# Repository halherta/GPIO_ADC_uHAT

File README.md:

# IO uHat for Raspberry Pi Zero 2W

An expansion board (uHat) for the Raspberry Pi Zero 2W that provides additional GPIO and analog input capabilities through I2C and SPI interfaces.

## Features

- **16 Additional GPIO Pins**: MCP23017 I2C GPIO expander
- **8-Channel 12-bit ADC**: MCP3208 SPI analog-to-digital converter
- **I2C EEPROM**: Compliant with Raspberry Pi uHat specification
- **Hand-Solder Friendly**: SOIC packages for ICs, 1206 packages for passives
- **3.3V Operation**: Compatible with Raspberry Pi GPIO voltage levels

## Hardware Specifications

### GPIO Expander (MCP23017)
- **Interface**: I2C
- **I2C Address**: 0x20
- **GPIO Pins**: 16 general-purpose input/output pins
- **Logic Level**: 3.3V only

### ADC (MCP3208)
- **Interface**: SPI
- **Channels**: 8 single-ended or 4 differential
- **Resolution**: 12-bit
- **Reference Voltage**: 3.3V
- **Input Range**: 0V to 3.3V

### Power Requirements
- **Supply Voltage**: 3.3V from Raspberry Pi
- **Power Source**: Raspberry Pi GPIO header

## Hardware Design

The board features a compact uHat form factor designed for the Raspberry Pi Zero 2W. All components use hand-solder-friendly packages:
- SOIC packages for integrated circuits
- 1206 packages for resistors and capacitors

### Documentation
- [Schematic (PDF)](https://hussamtalkstech.com/wp-content/uploads/GPIO_ADC_uHAT_schematic.pdf)
- KiCad design files available in this repository

## Software

### Python Classes

Two Python classes are provided for easy interfacing:

1. **MCP23017 GPIO Control**: Configure and control the 16 GPIO pins
2. **MCP3208 ADC Interface**: Perform analog-to-digital conversions

### Demo Application

A demonstration program is included that showcases the board's capabilities:
- Reads analog voltage from a potentiometer (connected to ADC)
- Controls a 10-LED bargraph display (connected to GPIO expander)
- LEDs illuminate proportionally to the input voltage (0V = all off, 3.3V = all on)

### Setup

```bash
# Enable I2C and SPI interfaces
sudo raspi-config
# Navigate to Interface Options and enable I2C and SPI

# Verify I2C device detection
i2cdetect -y 1
# Should show device at address 0x20

# Clone repository and run demo
git clone https://github.com/halherta/GPIO_ADC_uHAT
cd GPIO_ADC_uHAT/test_code
python3 demo.py
```

## Getting Started

### Prerequisites
- Raspberry Pi Zero 2W
- Python 3
- I2C and SPI interfaces enabled
- Required Python libraries:
  - `smbus2` (for I2C communication)
  - `spidev` (for SPI communication)

### Installation

1. Clone this repository:
```bash
git clone https://github.com/halherta/GPIO_ADC_uHAT
```

2. Install required Python packages:
```bash
pip3 install smbus2 spidev
```

3. Run the demo program:
```bash
cd test_code
python3 demo.py
```

## License

This project is open source and available for use under the terms specified in the repository.

## Related Posts

For more detailed information about this project, visit:
- [IO uHat Blog Post](https://hussamtalkstech.com/rpi-io-uhat/)
- Future posts will cover EEPROM configuration and additional applications

## Contributing

Contributions, issues, and feature requests are welcome!

- Designed with KiCad
- Compatible with Raspberry Pi uHat specification

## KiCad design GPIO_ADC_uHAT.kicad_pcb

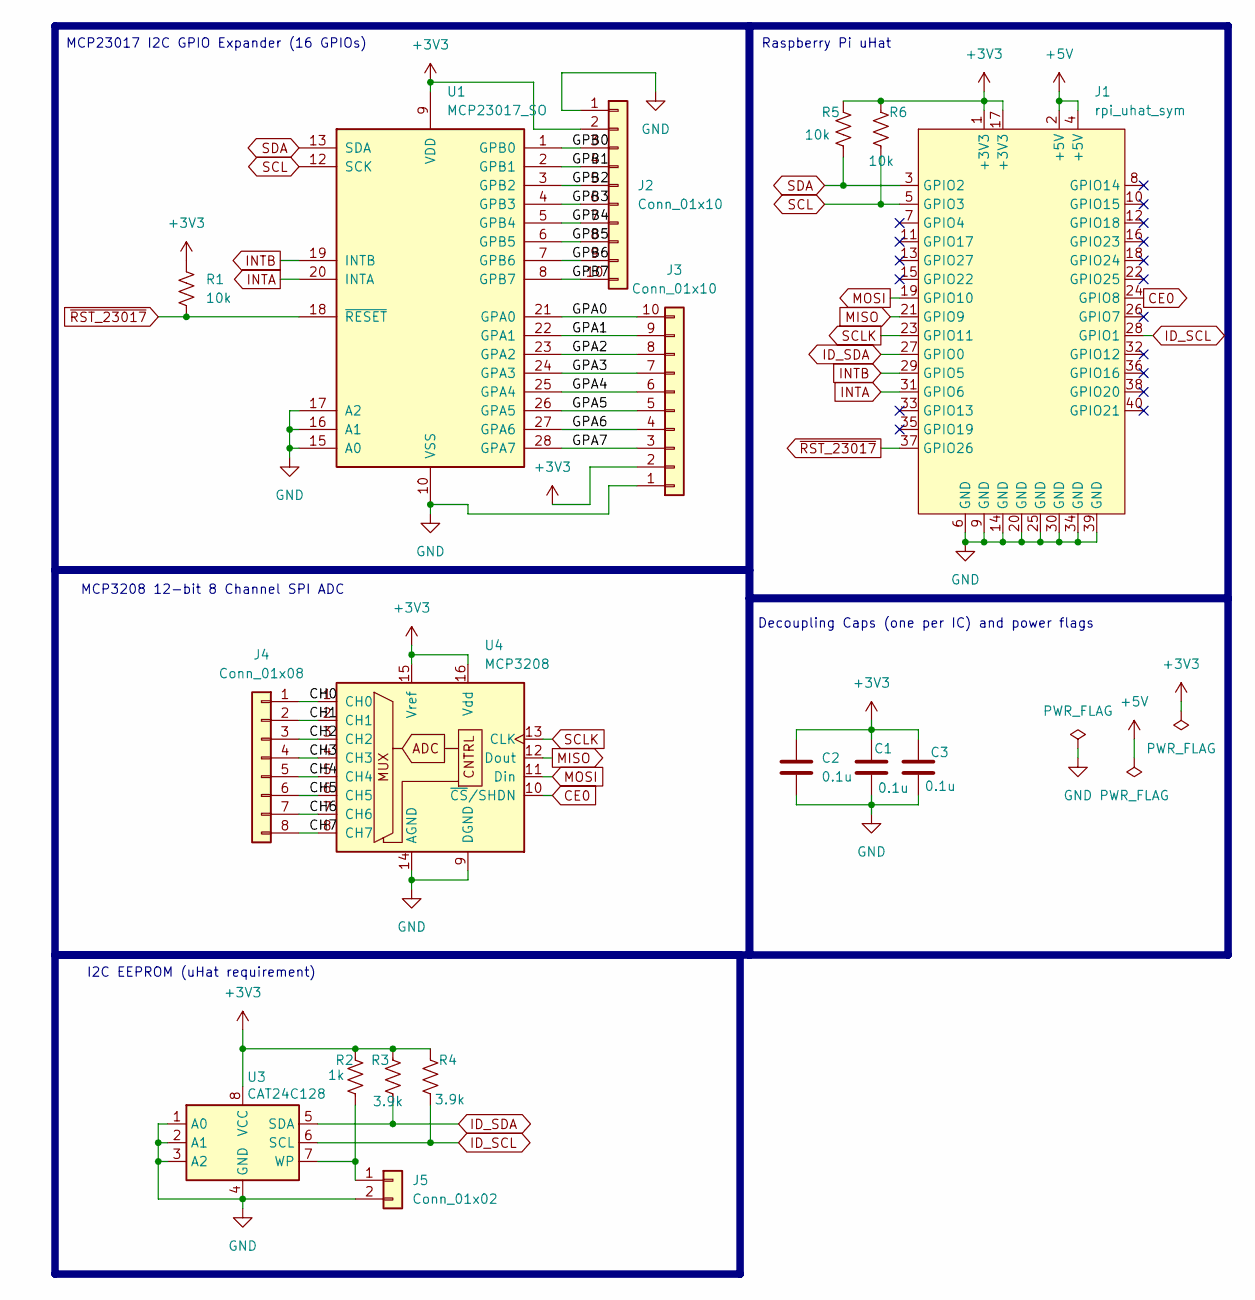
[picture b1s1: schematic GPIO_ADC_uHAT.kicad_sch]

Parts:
C1, C2, C3: 0.1u; C_1206_3216Metric_Pad1.33x1.80mm_HandSolder
J1: rpi_uhat_sym; rpi_uhat_fpt_v2
J2, J3: Conn_01x10; PinHeader_1x10_P2.54mm_Vertical
J4: Conn_01x08; PinHeader_1x08_P2.54mm_Vertical
J5: Conn_01x02; PinHeader_1x02_P2.54mm_Vertical
R1, R5, R6: 10k; R_1206_3216Metric_Pad1.30x1.75mm_HandSolder
R2: 1k; R_1206_3216Metric_Pad1.30x1.75mm_HandSolder
R3, R4: 3.9k; R_1206_3216Metric_Pad1.30x1.75mm_HandSolder
U1: MCP23017_SO; SOIC-28W_7.5x17.9mm_P1.27mm
U3: CAT24C128; SOIC-8_3.9x4.9mm_P1.27mm
U4: MCP3208; SOIC-16_3.9x9.9mm_P1.27mm

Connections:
+3V3: C1.1, C2.1, C3.1, J1.1 (+3V3), J1.17 (+3V3), J2.2, J3.2, R1.1, R2.1, R3.1, R4.1, R5.1, R6.1, U1.9 (VDD), U3.8 (VCC), U4.15 (Vref), U4.16 (Vdd)
+5V: J1.2 (+5V), J1.4 (+5V)
/CH0: J4.1, U4.1 (CH0)
/CH1: J4.2, U4.2 (CH1)
/CH2: J4.3, U4.3 (CH2)
/CH3: J4.4, U4.4 (CH3)
/CH4: J4.5, U4.5 (CH4)
/CH5: J4.6, U4.6 (CH5)
/CH6: J4.7, U4.7 (CH6)
/CH7: J4.8, U4.8 (CH7)
/GPA0: J3.10, U1.21 (GPA0)
/GPA1: J3.9, U1.22 (GPA1)
/GPA2: J3.8, U1.23 (GPA2)
/GPA3: J3.7, U1.24 (GPA3)
/GPA4: J3.6, U1.25 (GPA4)
/GPA5: J3.5, U1.26 (GPA5)
/GPA6: J3.4, U1.27 (GPA6)
/GPA7: J3.3, U1.28 (GPA7)
/GPB0: J2.3, U1.1 (GPB0)
/GPB1: J2.4, U1.2 (GPB1)
/GPB2: J2.5, U1.3 (GPB2)
/GPB3: J2.6, U1.4 (GPB3)
/GPB4: J2.7, U1.5 (GPB4)
/GPB5: J2.8, U1.6 (GPB5)
/GPB6: J2.9, U1.7 (GPB6)
/GPB7: J2.10, U1.8 (GPB7)
CE0: J1.24 (GPIO8), U4.10 (~CS/SHDN)
GND: C1.2, C2.2, C3.2, J1.6 (GND), J1.9 (GND), J1.14 (GND), J1.20 (GND), J1.25 (GND), J1.30 (GND), J1.34 (GND), J1.39 (GND), J2.1, J3.1, J5.2, U1.10 (VSS), U1.15 (A0), U1.16 (A1), U1.17 (A2), U3.1 (A0), U3.2 (A1), U3.3 (A2), U3.4 (GND), U4.9 (DGND), U4.14 (AGND)
ID_SCL: J1.28 (GPIO1), R4.2, U3.6 (SCL)
ID_SDA: J1.27 (GPIO0), R3.2, U3.5 (SDA)
INTA: J1.31 (GPIO6), U1.20 (INTA)
INTB: J1.29 (GPIO5), U1.19 (INTB)
MISO: J1.21 (GPIO9), U4.12 (Dout)
MOSI: J1.19 (GPIO10), U4.11 (Din)
unnamed: J5.1, R2.2, U3.7 (WP)
SCL: J1.5 (GPIO3), R6.2, U1.12 (SCK)
SCLK: J1.23 (GPIO11), U4.13 (CLK)
SDA: J1.3 (GPIO2), R5.2, U1.13 (SDA)
~RST_23017: J1.37 (GPIO26), R1.2, U1.18 (~RESET)

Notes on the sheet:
Decoupling Caps (one per IC) and power flags
MCP3208 12-bit 8 Channel SPI ADC
I2C EEPROM (uHat requirement)
Raspberry Pi uHat
MCP23017 I2C GPIO Expander (16 GPIOs)

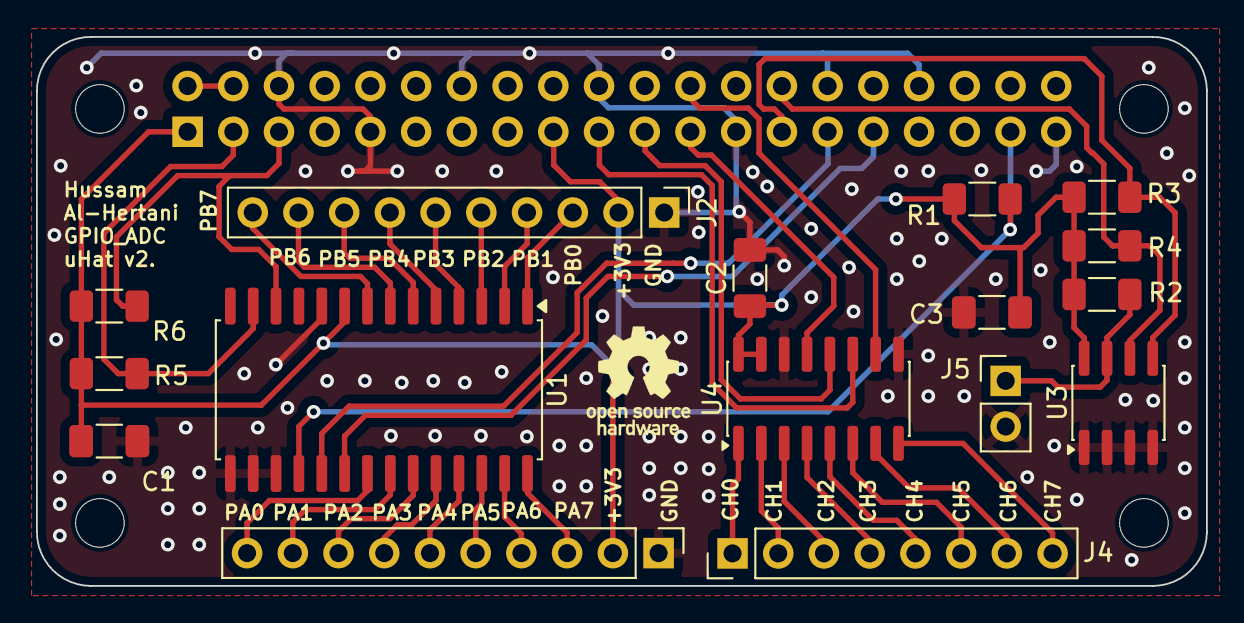
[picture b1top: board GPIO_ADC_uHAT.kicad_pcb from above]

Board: 2 copper layers, 65.0 x 30.5 mm, 17 parts (0 on the bottom side), 39 nets.

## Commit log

2025-11-06 made some modifications and added test code
2025-11-06 reduced backup files
2025-11-06 added pdf schematic
2025-11-08 Rename README to README.md
2025-12-07 addedd readme
2025-12-07 added readme
